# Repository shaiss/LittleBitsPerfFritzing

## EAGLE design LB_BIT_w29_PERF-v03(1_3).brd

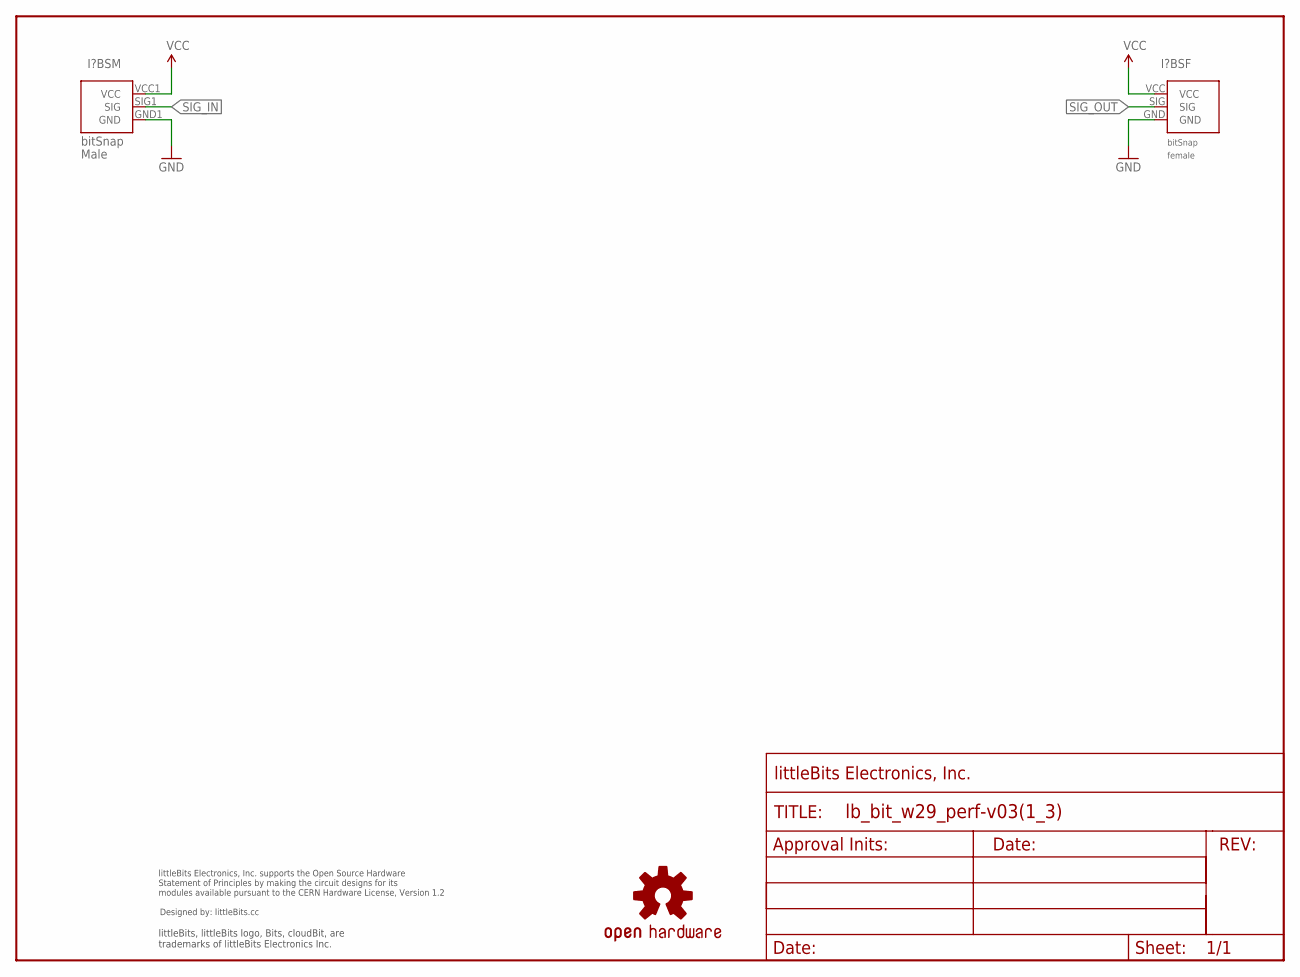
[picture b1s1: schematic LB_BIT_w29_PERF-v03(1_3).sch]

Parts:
I?BSF: BITSNAP_V03_FEMALE
I?BSM: BITSNAP_V03_MALE
U$1: OSHWCREDIT
U$2: OSHW-LOGOL; OSHW-LOGO-L
U$18: FRAME-LETTER-OHWOHW; FABDWG01-OHW

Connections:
GND: I?BSF.GND, I?BSM.GND1 (GND)
SIG_IN: I?BSM.SIG1 (SIG)
SIG_OUT: I?BSF.SIG
VCC: I?BSF.VCC, I?BSM.VCC1 (VCC)

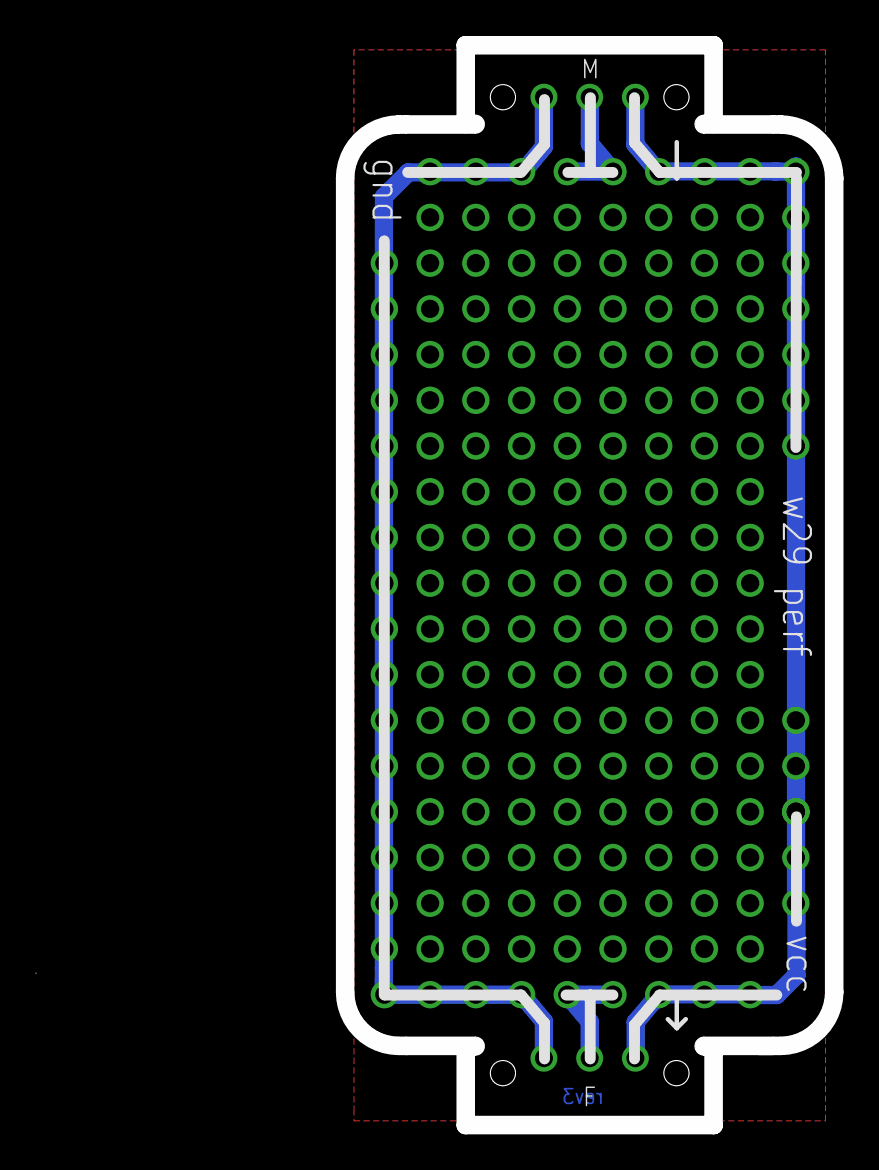
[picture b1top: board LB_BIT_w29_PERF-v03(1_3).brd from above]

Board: 2 copper layers, 43.9 x 60.0 mm, 7 parts (0 on the bottom side), 2 nets.

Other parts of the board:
DRILEGEND: DRILEGEND
U$11: OSHW_FILLX150_NOTEXT

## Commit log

2015-08-31 :confetti_ball: Added .gitattributes & .gitignore files

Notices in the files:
parts and their libraries:
LITTLEBITS: modules available pursuant to the CERN Hardware License,
Version 1.2
LITTLEBITS: modules available pursuant to the CERN Hardware License, Version 1.2
